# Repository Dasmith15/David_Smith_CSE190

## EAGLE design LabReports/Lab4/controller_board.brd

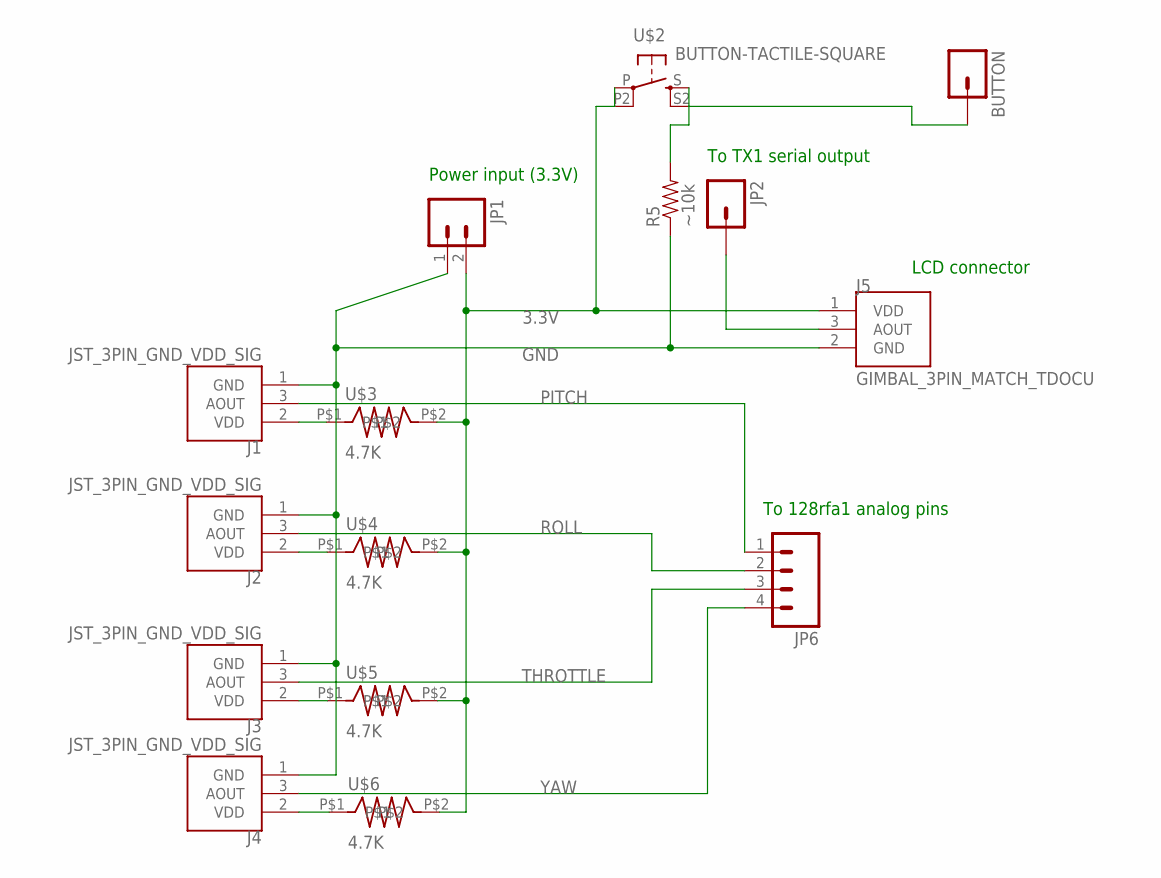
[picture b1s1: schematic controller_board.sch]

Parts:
BUTTON: M01PTH; 1X01
J1, J2, J3, J4: JST_3PIN_GND_VDD_SIG; JST-3-PTH-REVERSE
J5: GIMBAL_3PIN_MATCH_TDOCU; JST-3-PTH
JP1: M021X02_NO_SILK; 1X02_NO_SILK
JP2: M01PTH; 1X01
JP6: M04PTH; 1X04
R5: ~10k; AXIAL-0.4
U$2: BUTTON-TACTILE-SQUARE; BUTTON-TACTILE-SQUARE-ADAFRUIT1010
U$3, U$4, U$5, U$6: 4.7K; CRF12_RESISTOR

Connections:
3.3V: J5.1 (VDD), JP1.2, U$2.P, U$2.P2 (P1), U$3.P$2, U$4.P$2, U$5.P$2, U$6.P$2
GND: J1.1 (GND), J2.1 (GND), J3.1 (GND), J4.1 (GND), J5.2 (GND), JP1.1, R5.P$1 (1)
unnamed: J1.2 (VDD), U$3.P$1
unnamed: J2.2 (VDD), U$4.P$1
unnamed: J3.2 (VDD), U$5.P$1
unnamed: J4.2 (VDD), U$6.P$1
unnamed: BUTTON.1, R5.P$2 (2), U$2.S, U$2.S2 (S1)
unnamed: J5.3 (AOUT), JP2.1
PITCH: J1.3 (AOUT), JP6.1
ROLL: J2.3 (AOUT), JP6.2
THROTTLE: J3.3 (AOUT), JP6.3
YAW: J4.3 (AOUT), JP6.4

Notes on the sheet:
To 128rfa1 analog pins
LCD connector
Power input (3.3V)
To TX1 serial output

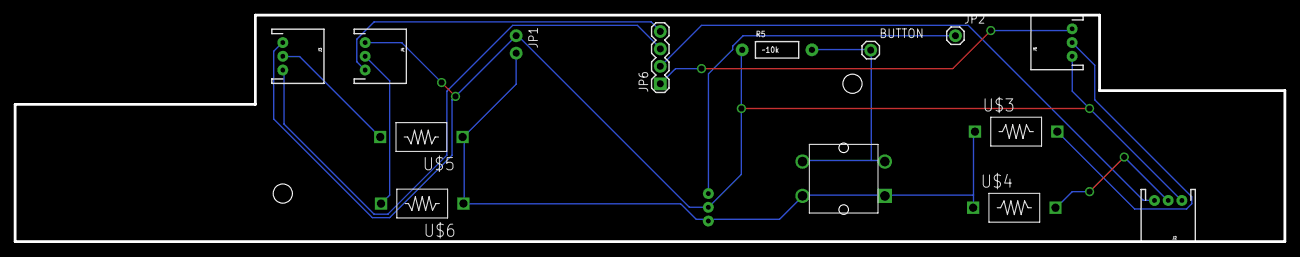
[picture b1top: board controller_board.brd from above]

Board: 2 copper layers, 185.0 x 33.0 mm, 16 parts (1 on the bottom side), 12 nets.

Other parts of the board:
U$1: CONNECTOR_BOARD_OUTLINE

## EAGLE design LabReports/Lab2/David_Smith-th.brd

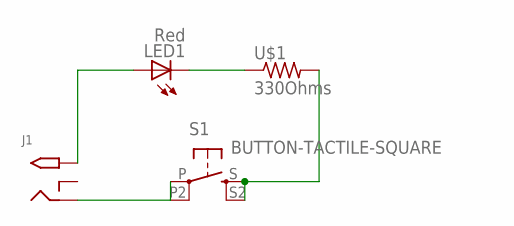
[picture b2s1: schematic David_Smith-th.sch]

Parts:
J1: 2.1MMJACKTHM; PJ-102A
LED1: Red; LED5MM
S1: BUTTON-TACTILE-SQUARE; BUTTON-TACTILE-SQUARE-ADAFRUIT1010
U$1: 330Ohms; RESAD1160W55L680D260_HS

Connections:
unnamed: LED1.K (C), U$1.1
unnamed: S1.S, S1.S2 (S1), U$1.2
unnamed: J1.RING, S1.P, S1.P2 (P1)
unnamed: J1.TIP, LED1.A

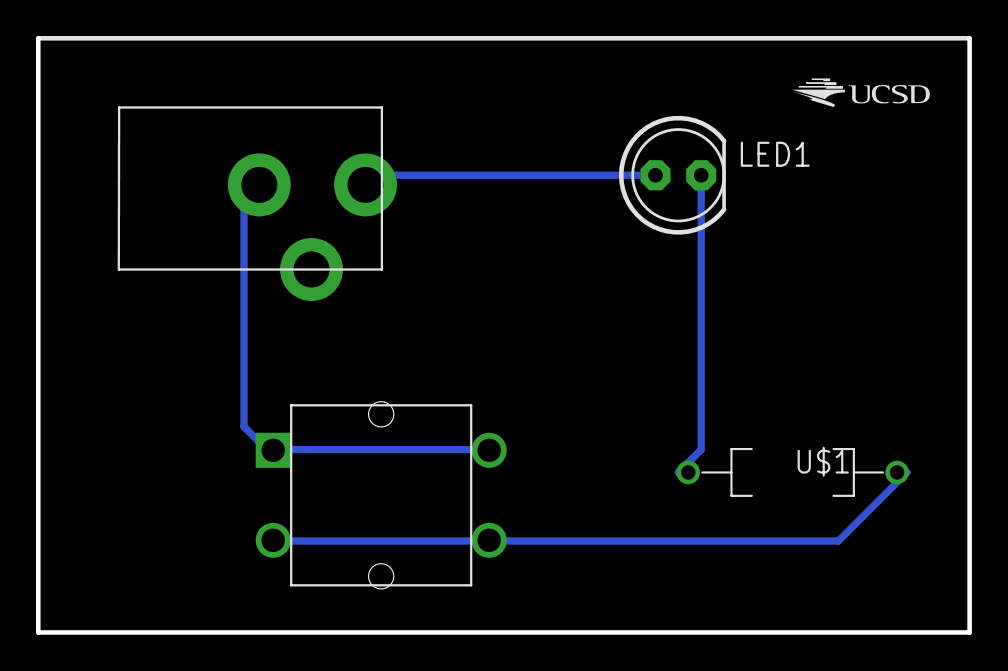
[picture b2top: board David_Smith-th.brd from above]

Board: 2 copper layers, 51.7 x 33.0 mm, 5 parts (0 on the bottom side), 4 nets.

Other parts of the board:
U$2: UCSD_LOGO

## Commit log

2015-04-10 Lab 3 code and data initial commit
2015-04-10 Lab 2 turnin to LabReports\Lab2
2015-04-10 Update Lab2 turnin
2015-04-13 Lab 3 turnin
2015-04-16 Lab4 initial turnin (no CAM files)
2015-04-16 Lab4: add cam files, mirror IMU pads

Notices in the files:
parts and their libraries:
SparkFun-Connectors: Licensing: Creative Commons ShareAlike 4.0 International - https://creativecommons.org/licenses/by-sa/4.0
